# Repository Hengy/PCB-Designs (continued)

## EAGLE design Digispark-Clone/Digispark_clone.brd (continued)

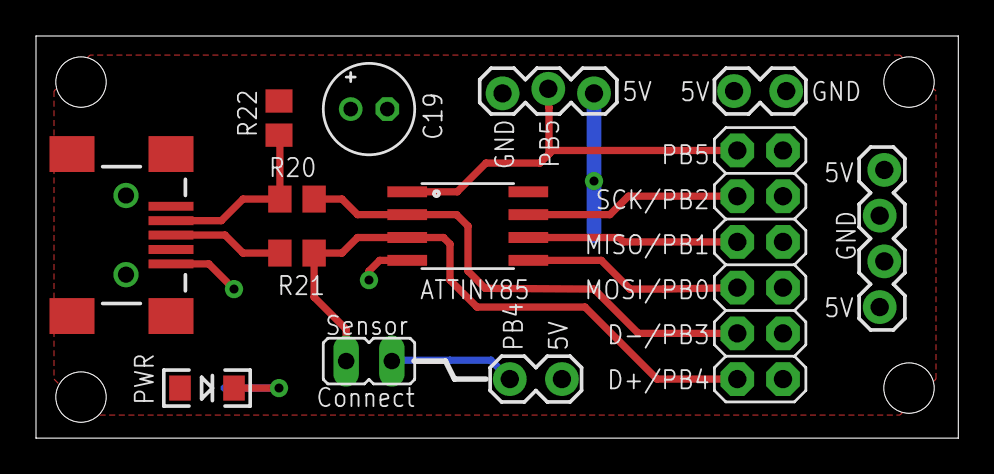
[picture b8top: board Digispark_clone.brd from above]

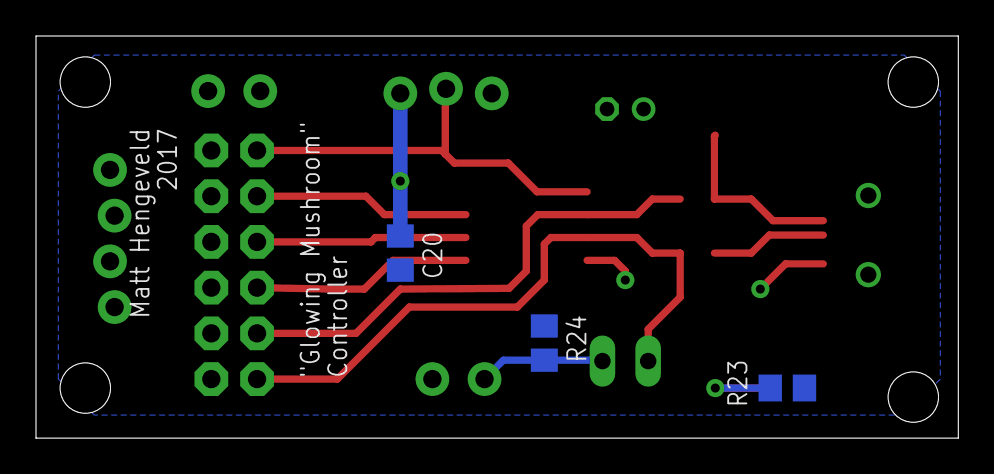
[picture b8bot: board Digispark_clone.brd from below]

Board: 2 copper layers, 51.2 x 22.3 mm, 16 parts (3 on the bottom side), 12 nets.

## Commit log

2017-04-06 OPA188
2017-04-06 ADS7822 Example Code
    Arduino code for testing the ADS7822
2017-04-06 MC34063 Step Up
2017-04-06 Update README.md
    Formatting
2017-04-06 Update README.md
    Update to main readme
2017-04-06 Digispark clone
2017-04-06 LM3916
2017-04-06 LM3916 LED PCBs
    PCB designed for 5mm square LEDs
2017-04-06 TLC5973
2017-04-06 TLC5973 Silkscreen Fix
    Fixed SDI/SDO silkscreen error
2017-04-06 Example Code
    Arduino and ESP8266 example code for controlling RGB LEDs
2017-04-06 TLC5973 example code & readmes
2017-04-06 ADT7302
2017-04-07 TPS61169 LED Driver
    3 PCB designs & readme
2017-04-09 Changed Op Amp
    CHanged op amp silkscreen and added readme
2017-04-20 MCP4922
    Added board for dual MCP4922 12-bit DACs
2017-04-20 Added jumper for voltage reference; readme
2017-04-28 LM3916 Update
    Gain stage, silkscreen
